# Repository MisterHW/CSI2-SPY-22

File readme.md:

# CSI2-SPY-22

> [!WARNING]  
> Rev.A layout and footprints have not been proven through prototyping yet. Replicate this design based on your own assessment. Follow the updates of this repository to be notified when more results have been added.

## CSI2-SPY-22-1A 

This board fundamentally has two variants integrated into a single PCB. It can be fully populated, or one one side can be left unpopulated. Only one side may be used at a time, since the six broken-out signals are shared, but this allows easy testing under similar conditions with and without the re-timer IC.

- Front side: passive FPC extender with I2C tapping
- Back side. active FPC extender based on the DPHY440 re-timer IC, with I2C tapping

## Raspberry Pi Camera Debugging

Prior work on https://github.com/jergling/MIPI-Spy offers a 15-pin, 1mm pitch PFC bridge PCB with probe points for all signals. RPI CM4 IO BOARD features one, Raspberry Pi 5 boards feature two 4-lane CSI2 camera ports using 22-pin, 0.5mm pitch FFC headers. 

To obtain access to the associated I2C lines and to be able to hook up a logic analyzer, a matching PCB design is provided in this repository.

## 22-Pin FPC Extender With I2C Connections

CSI2-SPY-22 is a 4-layer board that can be populated in multiple variants:
- front-ony: passive PCB with three headers J1, J2, J3.
- back-only: J3, J4, J5 plus [SN65DPHY440SS](https://www.ti.com/product/SN65DPHY440SS) MIPI® CSI-2/DSI DPHY retimer, LDO and passives. 

Re-timers can be used to zero out skew between lanes and re-transmit data with optional pre-emphasis. Please refer to  [DPHY440 datasheet](https://www.ti.com/lit/ds/symlink/sn65dphy440ss.pdf)  *8.2.2
Detailed Design Procedure* for an appropriate adaption via R1 thru R8.

	The output pins automatically compensate for uneven skew between clock and data lanes received on its 
	inputs ports. The DPHY440 output voltage swing and edge rate can be adjusted by changing the state of
	the VSADJ_CFG0 pin and ERC pin respectively.

Populate Q1 (DMG1024), R5 (2k) and R7 (2k) to enable I2C. 

[Rev-1A schematic (pdf version)](CSI2-SPY-22-1A/output/RevA_schematic.pdf)

## Raspberry Pi 5 Connectors

On The Raspberry Pi 5 board, the connector name labels J3 and J4 are not used as Pin 1 location indicators. 
- Note RPi 5 J3 and J4 Pin 1 locations are on the inward facing side of the ZIF FPC connectors.
- Orient CSI2-SPY-22 based on the Pin 1 and Pin 22 markings on the board.
- Use a **same-side 22-pin 0.5mm** pitch flex print cable to connect the CSI2-SPY-22 board HOST side to RPi 5 CAM/DISP headers.
- Erroenous connection (with an opposite-side flex print cable) will either lead to a disconnected state or the RPi 5 3.3V power rail will be shorted to GND.

Raspberry Pi 5 camera connectors:

## iBOM

via htmlpreview.github.io: [2024-03-24_bom/ibom.html](http://htmlpreview.github.io/?https://github.com/MisterHW/CSI2-SPY-22/blob/master/CSI2-SPY-22-1A/output/2024-03-24_bom/ibom.html) 

## License

KiCad project: copyright Helge Wurst 2024.

This source describes Open Hardware and is licensed under the CERN-OHL-S v2.

You may redistribute and modify this source and make products using it under the terms of the CERN-OHL-S v2 (https://ohwr.org/cern_ohl_s_v2.txt).

This source is distributed WITHOUT ANY EXPRESS OR IMPLIED WARRANTY, INCLUDING OF MERCHANTABILITY, SATISFACTORY QUALITY AND FITNESS FOR A PARTICULAR PURPOSE. Please see the CERN-OHL-S v2 for applicable conditions.

Source location: https://github.com/MisterHW/CSI2-SPY-22

As per CERN-OHL-S v2 section 4, should You produce hardware based on this source, You must where practicable maintain the Source Location visible on the external case of the Gizmo or other products you make using this source.

## Changes

- 2024-03 Rev. 1A release with part numbers and consolidated BOM
- 2024-02 Rev. 1A pre-release and initial documentation.

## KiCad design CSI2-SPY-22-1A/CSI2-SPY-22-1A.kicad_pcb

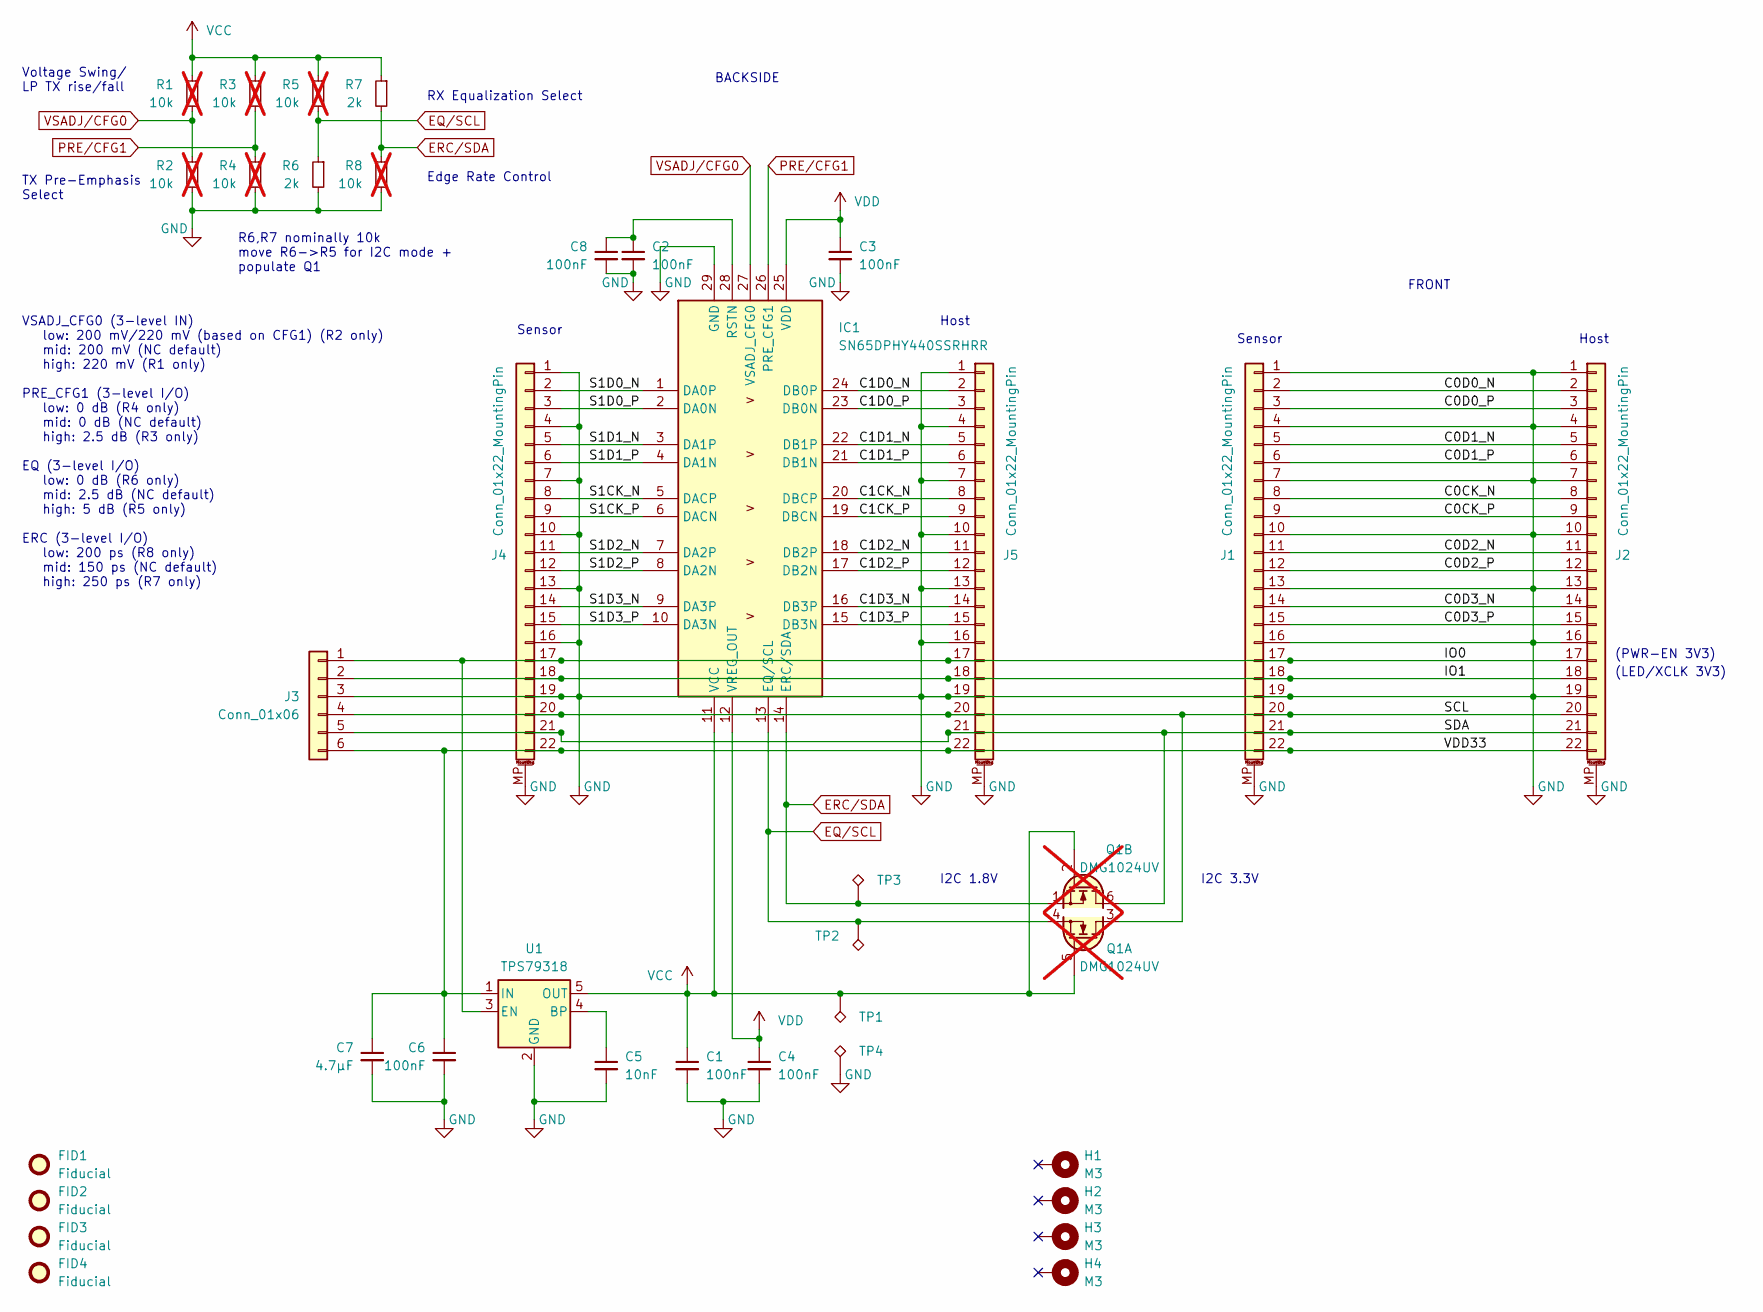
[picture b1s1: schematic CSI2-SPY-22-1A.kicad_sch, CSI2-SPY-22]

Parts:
C1, C2, C3, C4, C6, C8: 100nF; C_0402_1005Metric; Mouser Part Number 80-C0402C104K4R
C5: 10nF; C_0402_1005Metric; Mouser Part Number 81-GRM1555CYA103GE1D
C7: 4.7µF; C_0603_1608Metric; Mouser Part Number 581-0603YW475KAT2A
FID1, FID2, FID3, FID4: Fiducial; Fiducial_0.5mm_Mask1mm
H1, H2, H3, H4: M3; MountingHole_3.2mm_M3_DIN965_Pad
IC1: SN65DPHY440SSRHRR; WQFN28EP-RHR0028A; Manufacturer_Part_Number SN65DPHY440SSRHRR; Mouser Part Number 595-N65DPHY440SSRHRR
J1, J4: Conn_01x22_MountingPin; TE_2-1734839-2_1x22-1MP_P0.5mm_Horizontal; Mouser Part Number 649-F32Q-1A7H1-11022
J2, J5: Conn_01x22_MountingPin; TE_2-1734839-2_1x22-1MP_P0.5mm_Horizontal_TopContact_Reverse; Mouser Part Number 649-F32Q-1A7H1-11022
J3: Conn_01x06; PinHeader_1x06_P2.54mm_Horizontal; Mouser Part Number 649-1012937990602BLF
Q1: DMG1024UV; SOT-563; Mouser Part Number 621-DMG1024UV-7; not fitted
R1, R2, R3, R4, R5, R8: 10k; R_0603_1608Metric; Mouser Part Number 603-RC0603FR-07510KL; not fitted
R6, R7: 2k; R_0603_1608Metric; Mouser Part Number 71-CRCW0603-2.0K-E3
TP1, TP2, TP3, TP4: TestPoint_Alt; TestPoint_Pad_D1.0mm
U1: TPS79318; SOT-23-5; Mouser Part Number 595-TPS79318DBVREP

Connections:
/C0CK_N: J1.8, J2.8
/C0CK_P: J1.9, J2.9
/C0D0_N: J1.2, J2.2
/C0D0_P: J1.3, J2.3
/C0D1_N: J1.5, J2.5
/C0D1_P: J1.6, J2.6
/C0D2_N: J1.11, J2.11
/C0D2_P: J1.12, J2.12
/C0D3_N: J1.14, J2.14
/C0D3_P: J1.15, J2.15
/C1CK_N: IC1.20 (DBCP), J5.8
/C1CK_P: IC1.19 (DBCN), J5.9
/C1D0_N: IC1.24 (DB0P), J5.2
/C1D0_P: IC1.23 (DB0N), J5.3
/C1D1_N: IC1.22 (DB1P), J5.5
/C1D1_P: IC1.21 (DB1N), J5.6
/C1D2_N: IC1.18 (DB2P), J5.11
/C1D2_P: IC1.17 (DB2N), J5.12
/C1D3_N: IC1.16 (DB3P), J5.14
/C1D3_P: IC1.15 (DB3N), J5.15
/IO0: J1.17, J2.17, J3.1, J4.17, J5.17, U1.3 (EN)
/IO1: J1.18, J2.18, J3.2, J4.18, J5.18
/S1CK_N: IC1.5 (DACP), J4.8
/S1CK_P: IC1.6 (DACN), J4.9
/S1D0_N: IC1.1 (DA0P), J4.2
/S1D0_P: IC1.2 (DA0N), J4.3
/S1D1_N: IC1.3 (DA1P), J4.5
/S1D1_P: IC1.4 (DA1N), J4.6
/S1D2_N: IC1.7 (DA2P), J4.11
/S1D2_P: IC1.8 (DA2N), J4.12
/S1D3_N: IC1.9 (DA3P), J4.14
/S1D3_P: IC1.10 (DA3N), J4.15
/SCL: J1.20, J2.20, J3.4, J4.20, J5.20, Q1.3 (D2)
/SDA: J1.21, J2.21, J3.5, J4.21, J5.21, Q1.6 (D1)
/VDD33: C6.1, C7.1, J1.22, J2.22, J3.6, J4.22, J5.22, U1.1 (IN)
EQ/SCL: IC1.13 (EQ/SCL), Q1.4 (S2), R5.2, R6.1, TP2.1
ERC/SDA: IC1.14 (ERC/SDA), Q1.1 (S1), R7.2, R8.1, TP3.1
GND: C1.2, C2.2, C3.2, C4.2, C5.2, C6.2, C7.2, C8.2, IC1.29 (GND), J1.1, J1.4, J1.7, J1.10, J1.13, J1.16, J1.19, J1.MP (MountPin), J2.1, J2.4, J2.7, J2.10, J2.13, J2.16, J2.19, J2.MP (MountPin), J3.3, J4.1, J4.4, J4.7, J4.10, J4.13, J4.16, J4.19, J4.MP (MountPin), J5.1, J5.4, J5.7, J5.10, J5.13, J5.16, J5.19, J5.MP (MountPin), R2.2, R4.2, R6.2, R8.2, TP4.1, U1.2 (GND)
unnamed: C2.1, C8.1, IC1.28 (RSTN)
unnamed: C5.1, U1.4 (BP)
PRE/CFG1: IC1.26 (PRE_CFG1), R3.2, R4.1
VCC: C1.1, IC1.11 (VCC), Q1.2 (G1), Q1.5 (G2), R1.1, R3.1, R5.1, R7.1, TP1.1, U1.5 (OUT)
VDD: C3.1, C4.1, IC1.12 (VREG_OUT), IC1.25 (VDD)
VSADJ/CFG0: IC1.27 (VSADJ_CFG0), R1.2, R2.1

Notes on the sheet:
Sensor
Host
BACKSIDE
(PWR-EN 3V3)
(LED/XCLK 3V3)
I2C 1.8V
RX Equalization Select
Voltage Swing/ LP TX rise/fall
I2C 3.3V
TX Pre-Emphasis Select
FRONT
VSADJ_CFG0 (3-level IN) low: 200 mV/220 mV (based on CFG1) (R2 only) mid: 200 mV (NC default) high: 220 mV (R1 only) PRE_CFG1 (3-level I/O) low: 0 dB (R4 only) mid: 0 dB (NC default) high: 2.5 dB (R3 only) EQ (3-level I/O) low: 0 dB (R6 only) mid: 2.5 dB (NC default) high: 5 dB (R5 only) ERC (3-lev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
Edge Rate Control
R6,R7 nominally 10k move R6->R5 for I2C mode + populate Q1

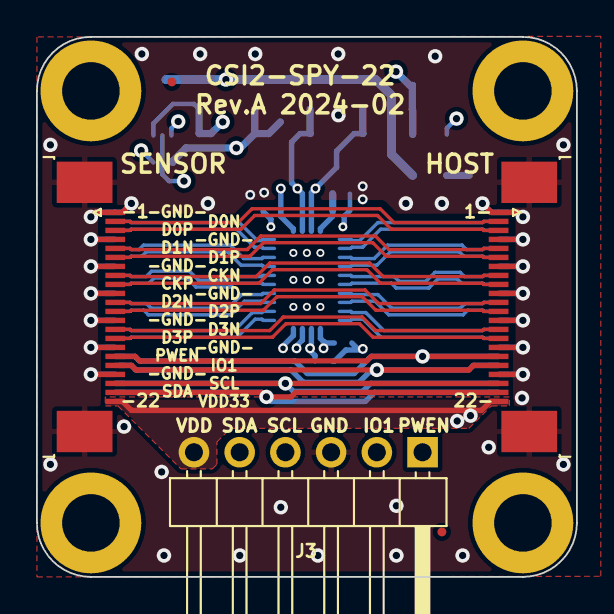
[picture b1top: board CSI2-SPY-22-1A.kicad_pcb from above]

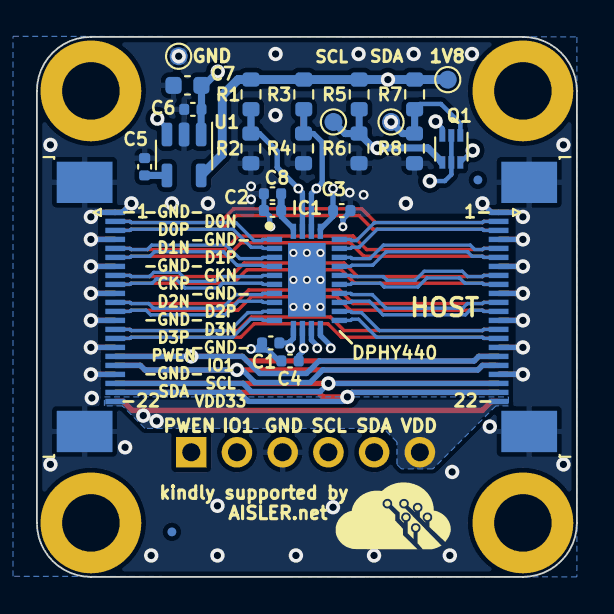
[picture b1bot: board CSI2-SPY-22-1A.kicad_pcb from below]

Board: 4 copper layers, 30.0 x 30.0 mm, 36 parts (27 on the bottom side), 44 nets.

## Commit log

2024-02-18 initial commit
    Rev.A project files as ordered from AISLER.net
2024-03-24 restructure project
2024-03-24 Rev-1A 2024-03 update
2024-03-24 update external links
    add iBOM preview and Aisler upload
2024-03-24 remove outdated duplicates
2024-03-24 fix order link
